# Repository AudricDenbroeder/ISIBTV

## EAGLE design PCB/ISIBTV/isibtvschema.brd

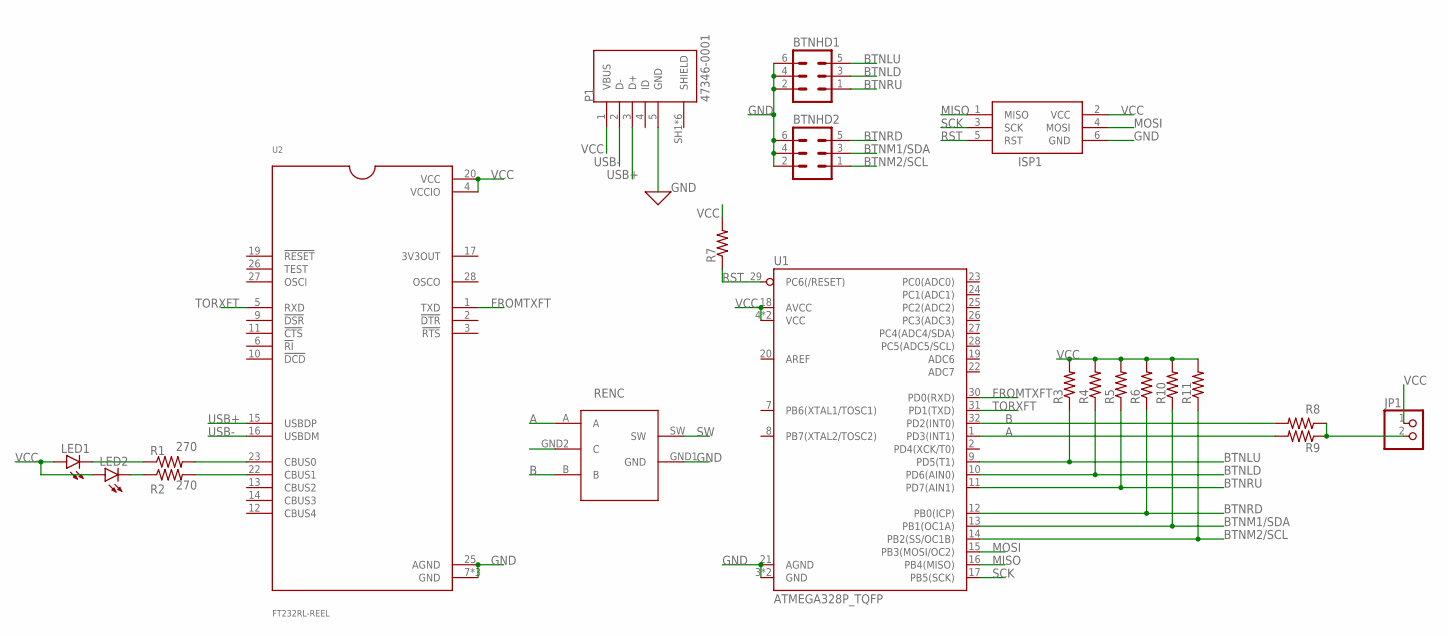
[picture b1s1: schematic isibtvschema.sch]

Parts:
BTNHD1, BTNHD2: MA03-2
ISP1: AVRISP-6; AVRISP
JP1: PINHD-1X2; 1X02
LED1, LED2: LED5MM
P1: 47346-0001; MOLEX_47346-0001
R1, R2: 270; 0207/10
R3, R4, R5, R6, R7, R8, R9, R10, R11: R-US_0207/10; 0207/10
RENC: RE11
U1: ATMEGA328P_TQFP; TQFP32-08
U2: FT232RL-REEL; SOP65P780X200-28N

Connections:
A: R9.2, RENC.A, U1.1 (PD3(INT1))
B: R8.2, RENC.B, U1.32 (PD2(INT0))
BTNLD: BTNHD1.3, R4.1, U1.10 (PD6(AIN0))
BTNLU: BTNHD1.5, R3.1, U1.9 (PD5(T1))
BTNM1/SDA: BTNHD2.3, R10.1, U1.13 (PB1(OC1A))
BTNM2/SCL: BTNHD2.1, R11.1, U1.14 (PB2(SS/OC1B))
BTNRD: BTNHD2.5, R6.1, U1.12 (PB0(ICP))
BTNRU: BTNHD1.1, R5.1, U1.11 (PD7(AIN1))
FROMTXFT: U1.30 (PD0(RXD)), U2.1 (TXD)
GND: BTNHD1.2, BTNHD1.4, BTNHD1.6, BTNHD2.2, BTNHD2.4, BTNHD2.6, ISP1.6 (GND), P1.5 (GND), RENC.GND1 (GND), RENC.GND2 (C), U1.3 (GND), U1.5 (GND), U1.21 (AGND), U2.7 (GND), U2.18 (GND), U2.21 (GND), U2.25 (AGND)
MISO: ISP1.1 (MISO), U1.16 (PB4(MISO))
MOSI: ISP1.4 (MOSI), U1.15 (PB3(MOSI/OC2))
unnamed: R1.2, U2.23 (CBUS0)
unnamed: R2.2, U2.22 (CBUS1)
unnamed: LED1.K (C), R1.1
unnamed: LED2.K (C), R2.1
unnamed: JP1.2, R8.1, R9.1
RST: ISP1.5 (RST), R7.1, U1.29 (PC6(/RESET))
SCK: ISP1.3 (SCK), U1.17 (PB5(SCK))
SW: RENC.SW
TORXFT: U1.31 (PD1(TXD)), U2.5 (RXD)
USB+: P1.3 (D+), U2.15 (USBDP)
USB-: P1.2 (D-), U2.16 (USBDM)
VCC: ISP1.2 (VCC), JP1.1, LED1.A, LED2.A, P1.1 (VBUS), R3.2, R4.2, R5.2, R6.2, R7.2, R10.2, R11.2, U1.4 (VCC), U1.6 (VCC), U1.18 (AVCC), U2.4 (VCCIO), U2.20 (VCC)

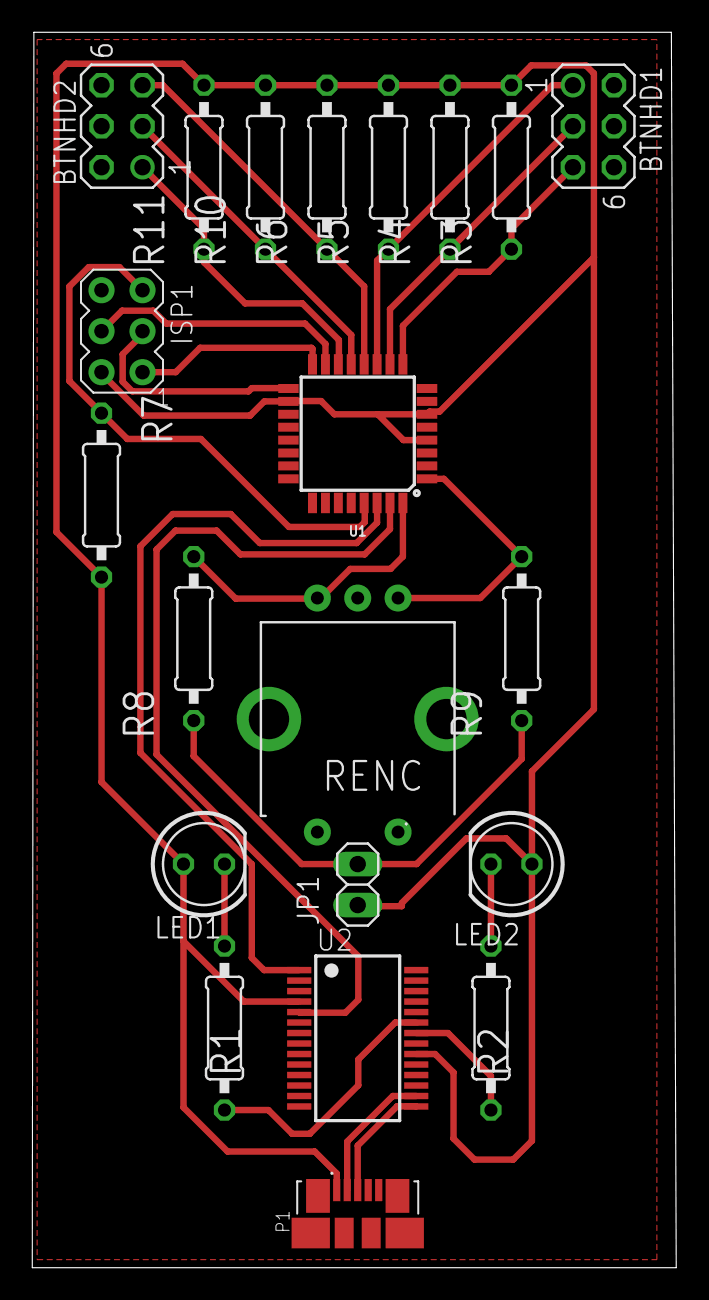
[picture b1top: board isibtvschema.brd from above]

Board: 2 copper layers, 39.9 x 76.5 mm, 21 parts (0 on the bottom side), 23 nets.

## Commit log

2019-12-15 Title Correction
2019-12-15 Correction
2019-12-18 Previous Files Outdated
2019-12-18 Updated Unity

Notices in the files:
parts and their libraries:
SparkFun-IC-Microcontroller: Licensing: Creative Commons ShareAlike 4.0 International - https://creativecommons.org/licenses/by-sa/4.0
